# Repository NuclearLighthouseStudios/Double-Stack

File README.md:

# Double Stack Distortion

These are the KiCAD schematics and board layout filed for my Double Stack Distortion pedal.  
If you just want the Gerber files or a PDF of the schematic check out the releases tab for downloads.

This PCB should be easily manufacturable with most online PCB houses by just uploading the gerber files.

This board is designed to be used with my Switchboard Pedal IO PCB which you can find [here](https://github.com/NuclearLighthouseStudios/Switchboard).

## BOM

| Reference     | Quantity | Value  | Description                                          |
| :------------ | -------: | -----: | :--------------------------------------------------- |
| C1 C7 C8      | 3        | 100n   | WIMA MKS2 63V                                        |
| C2 C4 C5      | 3        | 470n   | WIMA MKS2 50V                                        |
| C3 C6 C10     | 3        | 1µ     | WIMA MKS2 50V                                        |
| C9            | 1        | 1n     | WIMA FKP2 63V                                       |
| D1 D2 D3 D4   | 4        | 1N4148 | DO-35 Diode                                          |
| J1            | 1        |        | Pin Header, 6 pins, 2.54mm spacing                   |
| J2            | 1        |        | DC Barrel Jack with internal switch                  |
| Q1 Q2 Q3 Q4   | 4        | BC547B | 0.1A Ic, 45V Vce, Small Signal NPN Transistor, TO-92 |
| R1 R2 R11 R12 | 4        | 1M     | Metal film resistor 1%, DIN 0207                     |
| R10           | 1        | 390k   | Metal film resistor 1%, DIN 0207                     |
| R3 R7 R9 R13  | 4        | 10k    | Metal film resistor 1%, DIN 0207                     |
| R4            | 1        | 4.7k   | Metal film resistor 1%, DIN 0207                     |
| R5 R8         | 2        | 100k   | Metal film resistor 1%, DIN 0207                     |
| R6 R14        | 2        | 39k    | Metal film resistor 1%, DIN 0207                     |
| RV1 RV2       | 2        | 100k   | Alps RK09K1130C94 Potentiometer                      |

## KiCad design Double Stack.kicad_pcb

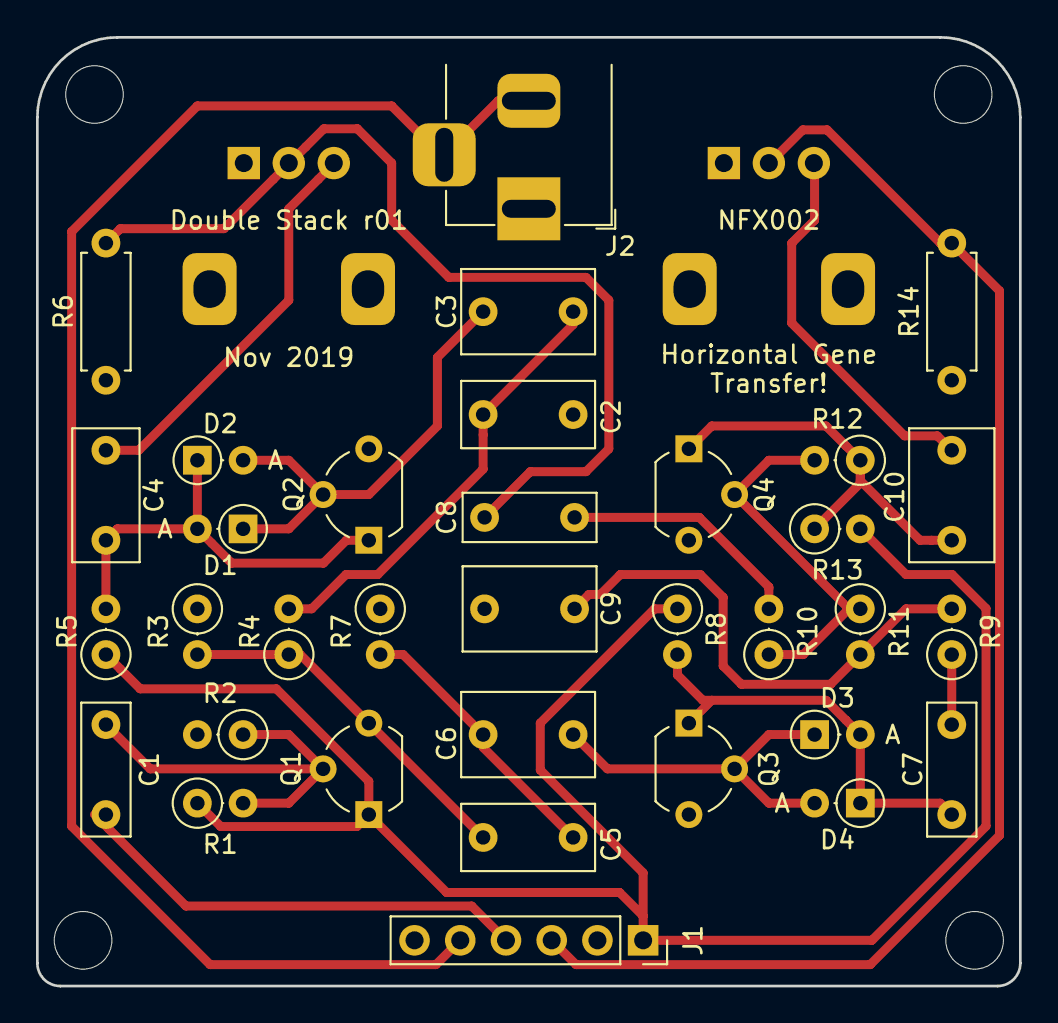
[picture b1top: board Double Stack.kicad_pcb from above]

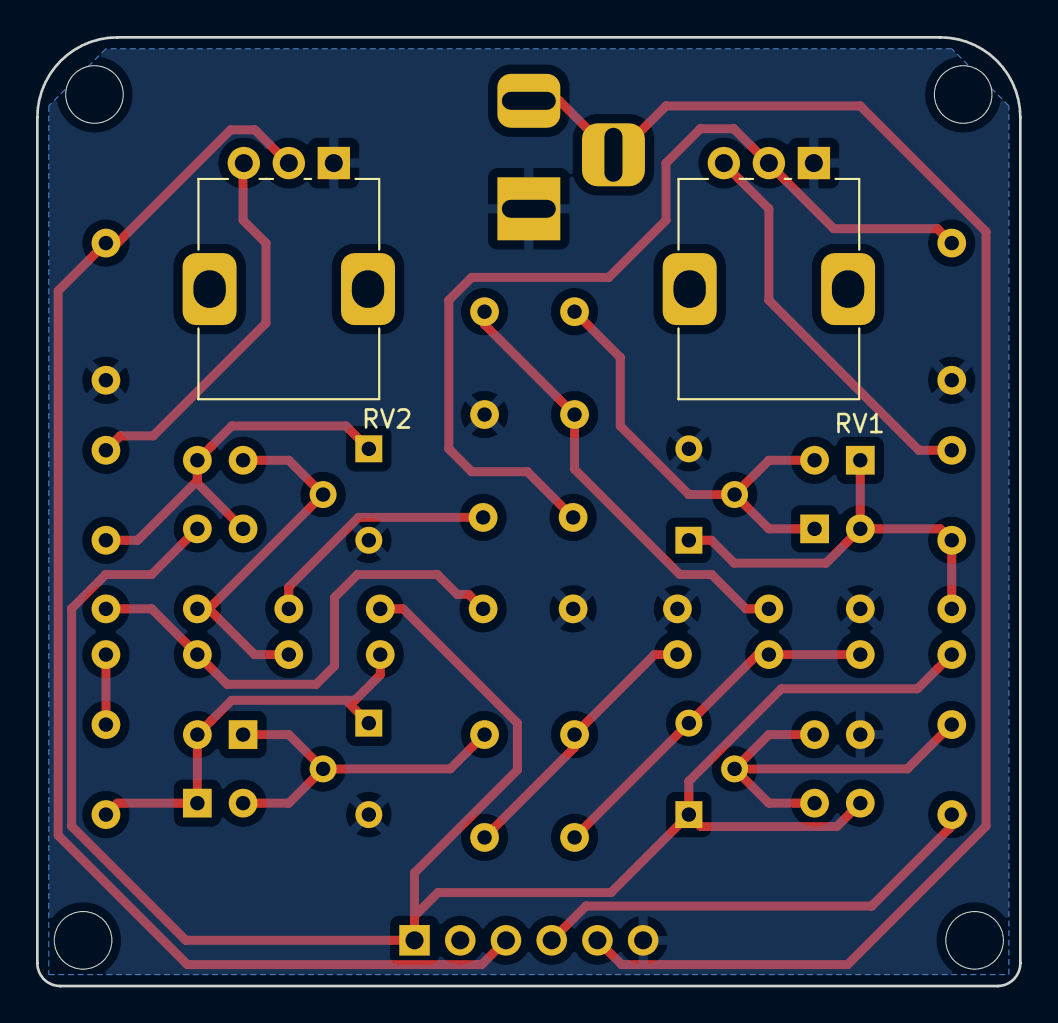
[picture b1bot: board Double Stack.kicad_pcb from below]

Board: 2 copper layers, 54.6 x 52.7 mm, 36 parts (2 on the bottom side), 21 nets.

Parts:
C1, C7, C8: 100n; C_Rect_L7.2mm_W2.5mm_P5.00mm_FKS2_FKP2_MKS2_MKP2
C2, C4, C5: 470n; C_Rect_L7.2mm_W3.5mm_P5.00mm_FKS2_FKP2_MKS2_MKP2
C3, C6, C10: 1µ; C_Rect_L7.2mm_W4.5mm_P5.00mm_FKS2_FKP2_MKS2_MKP2
C9: 1n; C_Rect_L7.2mm_W4.5mm_P5.00mm_FKS2_FKP2_MKS2_MKP2
D1, D2, D3, D4: 1N4148; D_DO-35_SOD27_P2.54mm_Vertical_AnodeUp
J1: Conn_01x06_Male; PinSocket_1x06_P2.54mm_Vertical
J2: Barrel_Jack_Switch; BarrelJack_Horizontal_Short
Q1, Q2, Q3, Q4: BC547; TO-92_Wide
R1, R2, R11, R12: 1M; R_Axial_DIN0207_L6.3mm_D2.5mm_P2.54mm_Vertical
R3, R7, R9, R13: 10k; R_Axial_DIN0207_L6.3mm_D2.5mm_P2.54mm_Vertical
R4: 4.7k; R_Axial_DIN0207_L6.3mm_D2.5mm_P2.54mm_Vertical
R5, R8: 100k; R_Axial_DIN0207_L6.3mm_D2.5mm_P2.54mm_Vertical
R6, R14: 39k; R_Axial_DIN0207_L6.3mm_D2.5mm_P7.62mm_Horizontal
R10: 390k; R_Axial_DIN0207_L6.3mm_D2.5mm_P2.54mm_Vertical
RV1, RV2: 100k; Potentiometer_Alps_RK09K_Single_Vertical

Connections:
+9V: J1.5, J2.2, J2.3
+9VA: J1.1, Q1.1 (C), R1.1, R5.1, R8.1, R13.2
BuffOut: C5.2, Q1.3 (E), R3.2, R4.1
GND: C2.2, C9.2, J1.6, J2.1, Q2.3 (E), Q3.3 (E), Q4.3 (E), R2.2, R3.1, R6.1, R7.1, R14.1, RV1.1, RV2.1
Input: C1.2, J1.4
LOut: C8.2, R6.2, RV1.2
unnamed: C1.1, Q1.2 (B), R1.2, R2.1
unnamed: C2.1, C3.2, R4.2
unnamed: C3.1, D1.1 (K), D2.2 (A), Q2.2 (B)
unnamed: C4.1, RV1.3
unnamed: C4.2, D1.2 (A), D2.1 (K), Q2.1 (C), R5.2
unnamed: C5.1, C6.2, R7.2
unnamed: C6.1, D3.1 (K), D4.2 (A), Q3.2 (B)
unnamed: C7.1, R9.1
unnamed: C7.2, D3.2 (A), D4.1 (K), Q3.1 (C), R8.2
unnamed: C8.1, R10.2
unnamed: C9.1, R9.2, R11.2
unnamed: C10.1, RV2.3
unnamed: C10.2, Q4.1 (C), R12.1, R13.1
unnamed: Q4.2 (B), R10.1, R11.1, R12.2
Output: J1.3, R14.2, RV2.2

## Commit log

2020-12-31 Fix capacitor types and voltages
2021-04-04 Fix C9 voltage rating in BOM
2022-08-14 Migrate to KiCAD 6

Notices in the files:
Double Stack.kicad_pcb:
CC BY-NC-SA
